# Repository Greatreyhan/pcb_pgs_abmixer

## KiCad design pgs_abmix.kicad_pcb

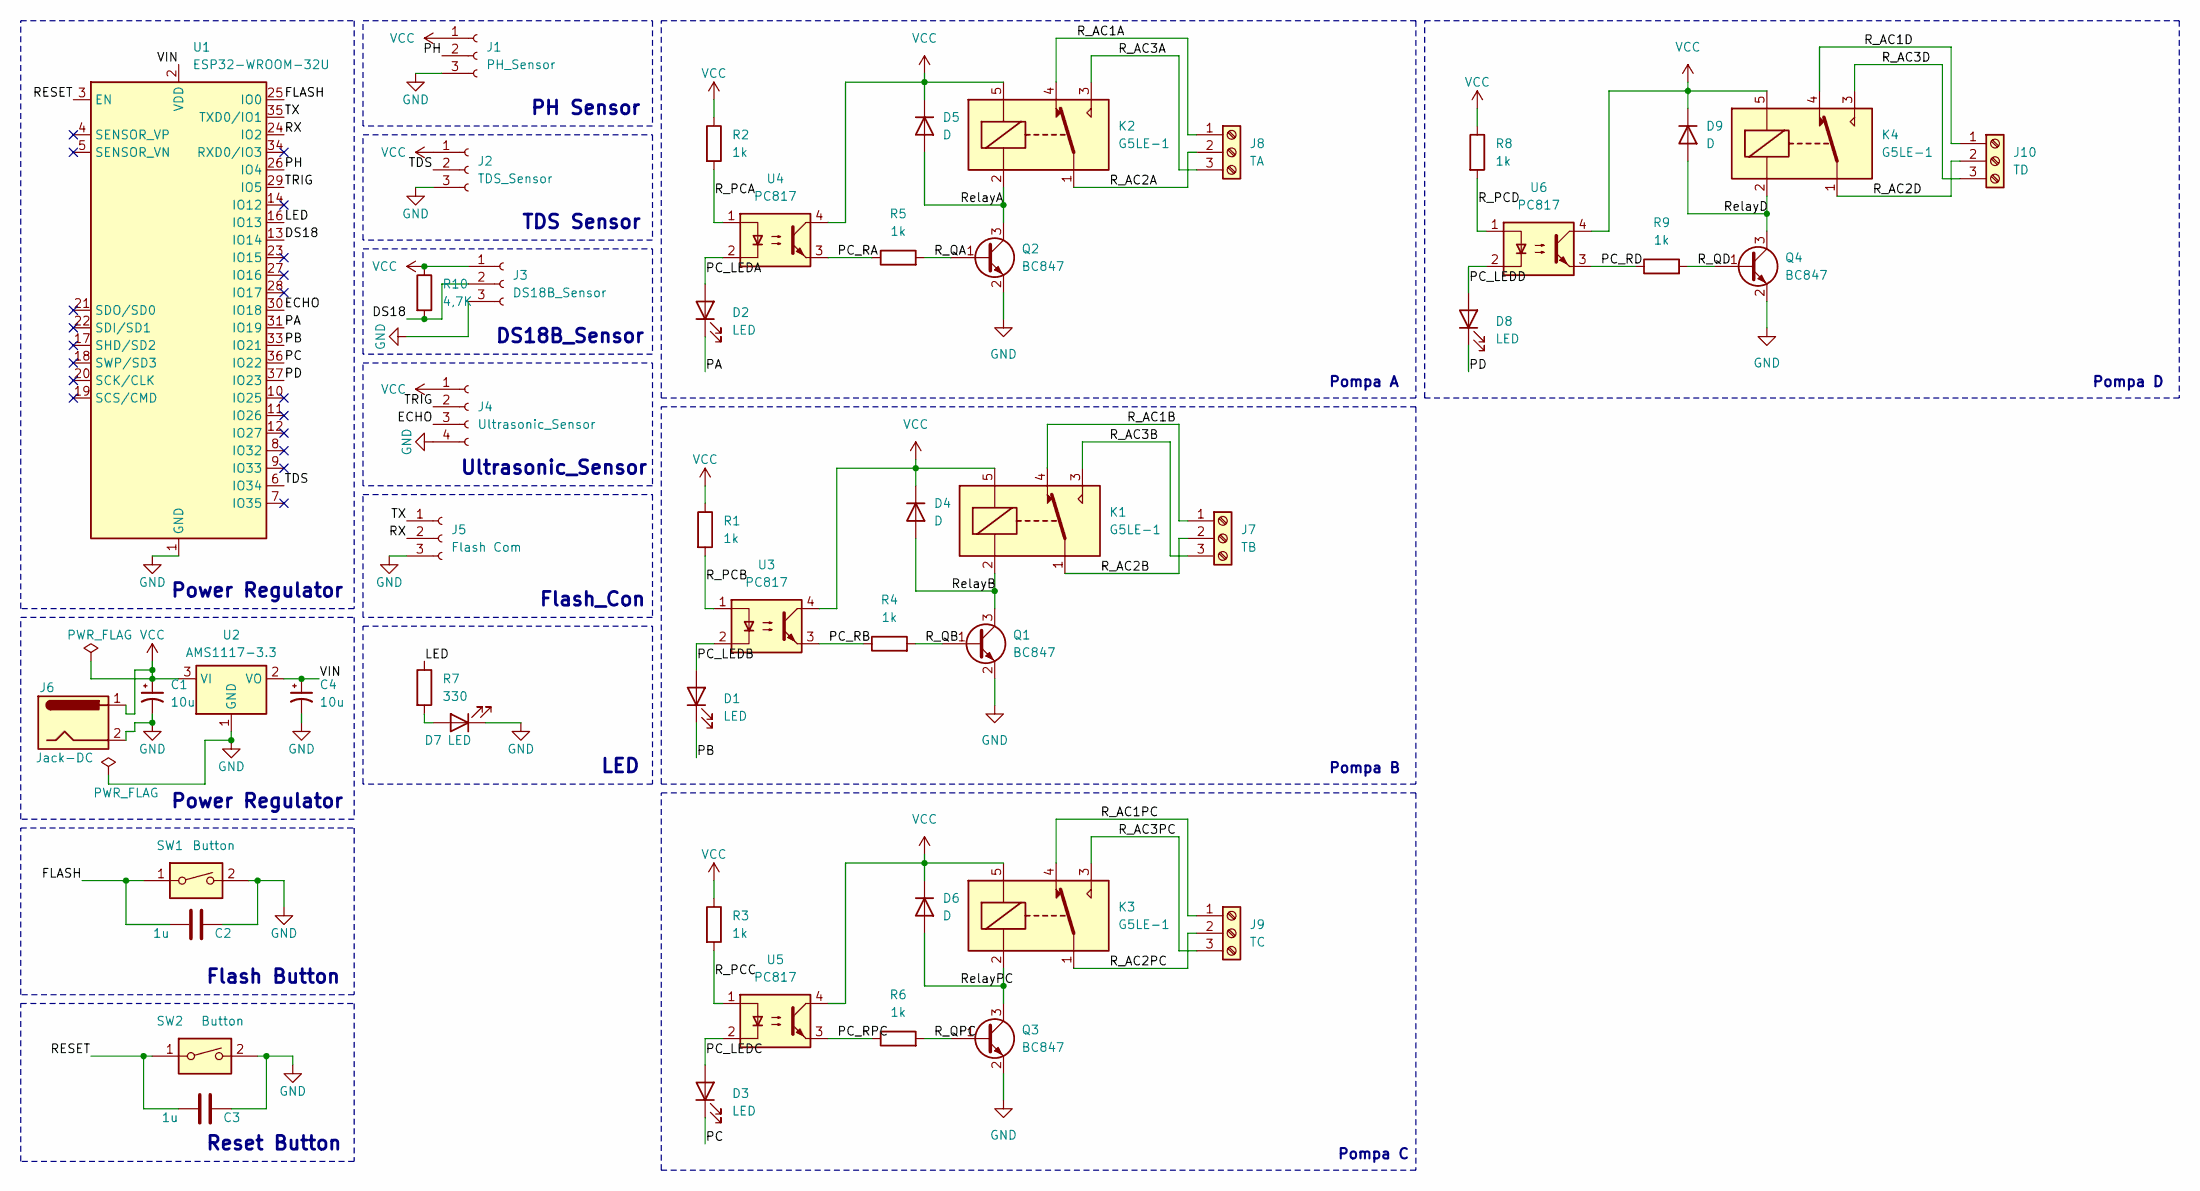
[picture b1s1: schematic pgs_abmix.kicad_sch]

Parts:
C1, C4: 10u; CP_Elec_4x5.3
C2, C3: 1u; C_1206_3216Metric_Pad1.33x1.80mm_HandSolder
D1, D2, D3, D7, D8: LED; LED_1206_3216Metric_Pad1.42x1.75mm_HandSolder
D4, D5, D6, D9: D; D_SMA_Handsoldering
J1: PH_Sensor; PinHeader_1x03_P2.54mm_Vertical
J2: TDS_Sensor; PinHeader_1x03_P2.54mm_Vertical
J3: DS18B_Sensor; PinHeader_1x03_P2.54mm_Vertical
J4: Ultrasonic_Sensor; PinSocket_1x04_P2.54mm_Vertical
J5: Flash Com; PinHeader_1x03_P2.54mm_Vertical
J6: Jack-DC; BarrelJack_SwitchcraftConxall_RAPC10U_Horizontal
J7: TB; TerminalBlock_bornier-3_P5.08mm
J8: TA; TerminalBlock_bornier-3_P5.08mm
J9: TC; TerminalBlock_bornier-3_P5.08mm
J10: TD; TerminalBlock_bornier-3_P5.08mm
K1, K2, K3, K4: G5LE-1; Relay_SPDT_Omron-G5LE-1
Q1, Q2, Q3, Q4: BC847; SOT-23
R1, R2, R3, R4, R5, R6, R8, R9: 1k; R_1206_3216Metric_Pad1.30x1.75mm_HandSolder
R7: 330; R_1206_3216Metric_Pad1.30x1.75mm_HandSolder
R10: 4,7K; R_1206_3216Metric_Pad1.30x1.75mm_HandSolder
SW1, SW2: Button; SW_Push_1P1T_NO_CK_KSC6xxJ
U1: ESP32-WROOM-32U
U2: AMS1117-3.3; SOT-223-3_TabPin2
U3, U4, U5, U6: PC817; DIP-4_W7.62mm

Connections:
/DS18: J3.2, R10.2, U1.13 (IO14)
/ECHO: J4.3, U1.30 (IO18)
/FLASH: C2.2, SW1.1, U1.25 (IO0)
/LED: R7.1, U1.16 (IO13)
/PA: D2.1 (K), U1.31 (IO19)
/PB: D1.1 (K), U1.33 (IO21)
/PC: D3.1 (K), U1.36 (IO22)
/PC_LEDA: D2.2 (A), U4.2
/PC_LEDB: D1.2 (A), U3.2
/PC_LEDC: D3.2 (A), U5.2
/PC_LEDD: D8.2 (A), U6.2
/PC_RA: R5.1, U4.3
/PC_RB: R4.1, U3.3
/PC_RD: R9.1, U6.3
/PC_RPC: R6.1, U5.3
/PD: D8.1 (K), U1.37 (IO23)
/PH: J1.2, U1.26 (IO4)
/RESET: C3.2, SW2.1, U1.3 (EN)
/RX: J5.2, U1.24 (IO2)
/R_AC1A: J8.1, K2.4
/R_AC1B: J7.1, K1.4
/R_AC1D: J10.1, K4.4
/R_AC1PC: J9.1, K3.4
/R_AC2A: J8.2, K2.1
/R_AC2B: J7.2, K1.1
/R_AC2D: J10.2, K4.1
/R_AC2PC: J9.2, K3.1
/R_AC3A: J8.3, K2.3
/R_AC3B: J7.3, K1.3
/R_AC3D: J10.3, K4.3
/R_AC3PC: J9.3, K3.3
/R_PCA: R2.2, U4.1
/R_PCB: R1.2, U3.1
/R_PCC: R3.2, U5.1
/R_PCD: R8.2, U6.1
/R_QA: Q2.1 (B), R5.2
/R_QB: Q1.1 (B), R4.2
/R_QD: Q4.1 (B), R9.2
/R_QPC: Q3.1 (B), R6.2
/RelayA: D5.2 (A), K2.2, Q2.3 (C)
/RelayB: D4.2 (A), K1.2, Q1.3 (C)
/RelayD: D9.2 (A), K4.2, Q4.3 (C)
/RelayPC: D6.2 (A), K3.2, Q3.3 (C)
/TDS: J2.2, U1.6 (IO34)
/TRIG: J4.2, U1.29 (IO5)
/TX: J5.1, U1.35 (TXD0/IO1)
/VIN: C4.1, U1.2 (VDD), U2.2 (VO)
GND: C1.2, C2.1, C3.1, C4.2, D7.1 (K), J1.3, J2.3, J3.3, J4.4, J5.3, J6.2, Q1.2 (E), Q2.2 (E), Q3.2 (E), Q4.2 (E), SW1.2, SW2.2, U1.1 (GND), U1.15 (GND), U1.38 (GND), U1.39 (GND), U2.1 (GND)
unnamed: D7.2 (A), R7.2
VCC: C1.1, D4.1 (K), D5.1 (K), D6.1 (K), D9.1 (K), J1.1, J2.1, J3.1, J4.1, J6.1, K1.5, K2.5, K3.5, K4.5, R1.1, R2.1, R3.1, R8.1, R10.1, U2.3 (VI), U3.4, U4.4, U5.4, U6.4

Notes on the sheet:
TDS Sensor
Ultrasonic_Sensor
Flash Button
Pompa C
Pompa D
Reset Button
LED
PH Sensor
Flash_Con
Pompa B
Power Regulator
Pompa A
DS18B_Sensor

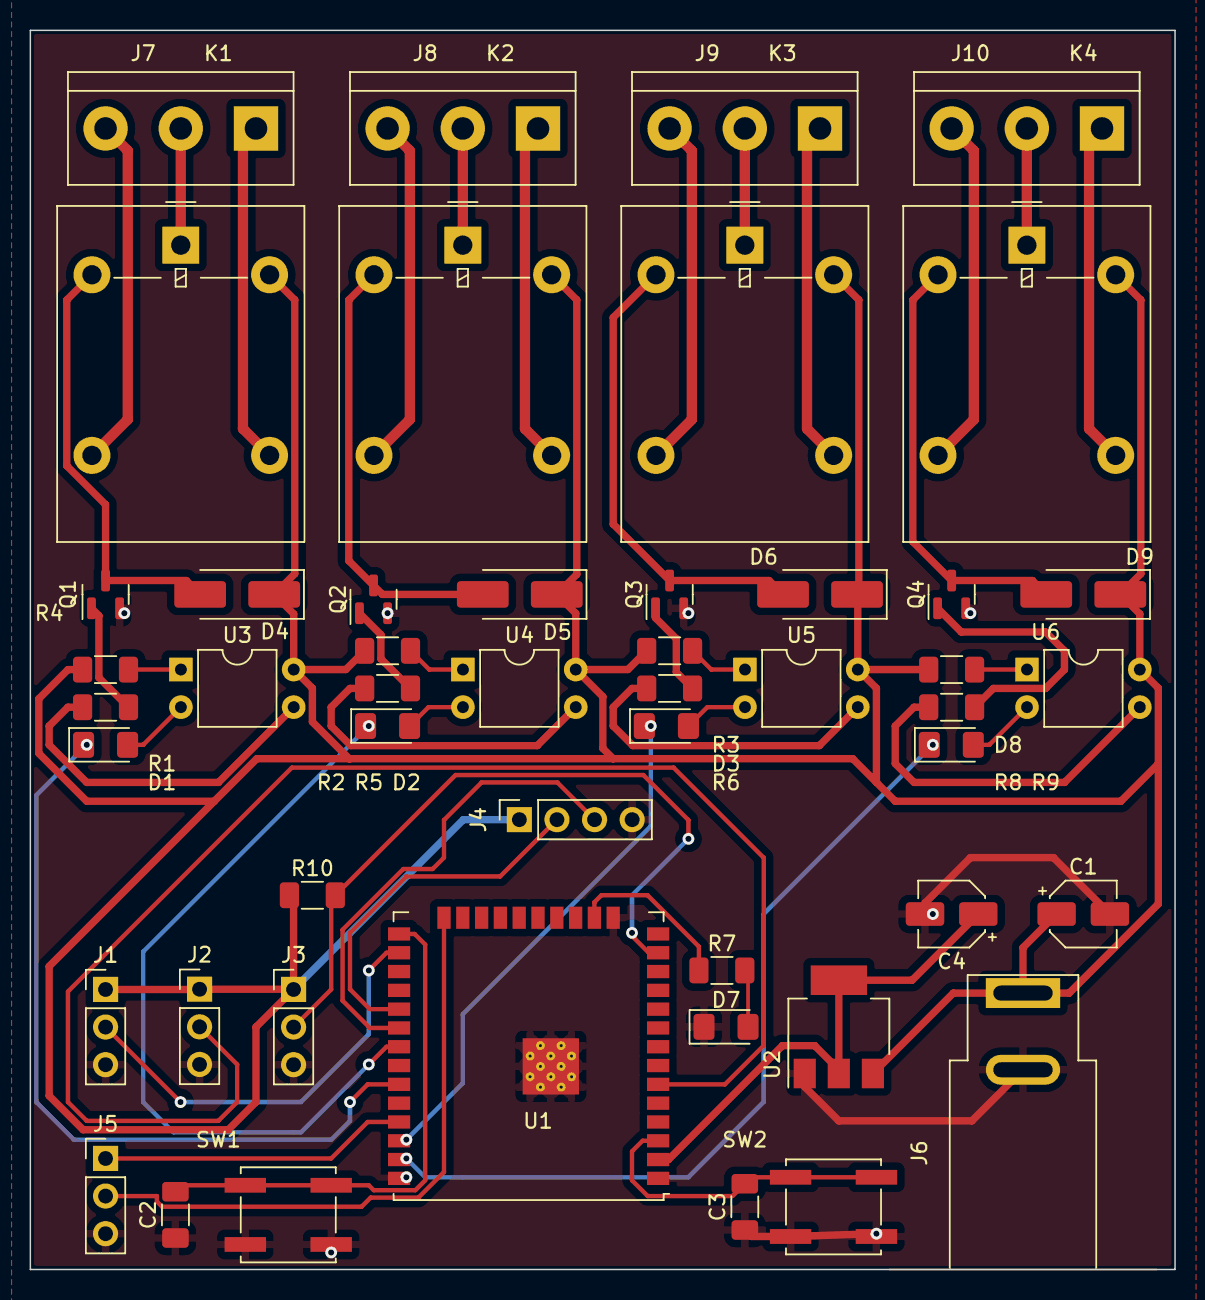
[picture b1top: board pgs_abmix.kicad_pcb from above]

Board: 2 copper layers, 77.3 x 83.7 mm, 49 parts (0 on the bottom side), 50 nets.

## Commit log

2023-08-16 schematic done
2023-08-17 pcb fixed
